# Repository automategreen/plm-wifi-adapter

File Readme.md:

WiFi Adapter for an Insteon PLM
===============
> A Spark Core WiFi adapter for an Insteon PLM
***

With the release of Insteon's newest Hub, Insteon removed the Hub's PLM interface.  This adapter adds secure access over WiFi to an Insteon PLM.

The adapter is a quick demo of what an Insteon compatible open hub could do.  We are currently working on an Open Source Hub with native support for the Insteon RF.

## Insteon Over the Spark Cloud

To improve on the standard Insteon Hub, we've used the awesome [Spark OS](https://www.spark.io/) to extend the PLM interface security to the cloud.  No unencrypted open information here. All messaging pass securely to and from the Spark OS.

### Insteon Message

All Insteon messages are sent as HEX strings.  The HEX strings allow for all Insteon messages to fit within the Spark OS packet restriction.  It also minimizes the logic for the adapter.

Because the HEX is cryptic and requires an in-depth knowledge of the Insteon HEX commands, we're adding support for the adapter to our Node.js module, [home-controller](https://github.com/automategreen/home-controller).

### Sending an Insteon Command

All the Insteon commands can be sent using HEX strings.

For example, to turn an Insteon switch on, you send a direct command to turn on the device.

```
$ spark call 0123456789ABCDEFGHI insteon 0262AABBCC0F117F
8
```

- Direct command: 0262
- Device ID: AABBCC
- Flags: 0F
- Action (turn on): 11
- Level (50%): 7F

The light turns on to 50%, and the call returns the number of bytes sent to the PLM. In this case `8`. 

### Receiving an Insteon Event

Now you can control your device, but you want more.  You want notifications in real time of from you devices.  No problem.  You can use the Spark OS subscribe to receive Insteon messages from your device.

Here's and example of getting notified of motion detected by a motion sensor.

```
$ spark subscribe insteon 0123456789ABCDEFGHI
Subscribing to "insteon" from 0123456789ABCDEFGHI's stream
Listening to: /v1/devices/0123456789ABCDEFGHI/events/insteon
{"name":"insteon","data":"0250aabbcc000001cf1101","ttl":"60","published_at":"2015-01-12T21:16:48.361Z","coreid":"0123456789ABCDEFGHI"}
```

The data field contains the Insteon message.

- Received command: 0250
- Device ID: AABBCC
- Group: 000001
- Flags: cf
- Action (motion detected): 11

### Insteon Request/Response

If you want to query a device for information, you combine the `call` and `subscribe` together. 

First, make sure you're subscribed.

```
spark subscribe insteon 0123456789ABCDEFGHI
Subscribing to "insteon" from 0123456789ABCDEFGHI's stream
Listening to: /v1/devices/0123456789ABCDEFGHI/events/insteon
```

Then, send the request. For example, get the light level.

```
$ spark call 0123456789ABCDEFGHI insteon 0262aabbcc0f1900
2
```

You'll then receive the Insteon response from the subscription.

```
{"name":"insteon","data":"0250aabbccffffff2f01ff","ttl":"60","published_at":"2015-01-12T21:16:48.361Z","coreid":"0123456789ABCDEFGHI"}
```

Light is on at 100%.  

If your want an easier way, you can use [home-controller](https://github.com/automategreen/home-controller).

## Native PLM Interface

The original Hub had an unsecured PLM interface, which allowed for the same communication on the LAN.  We can duplicate the interface on the Spark Core. By default, this interface is disabled (for security).  To enable it, place a simple Spark OS call.

```
spark call 55ff71066678505519401367 config plm=true
```

This call enables the PLM TCP interface (port 9761).

You can now use the adapter with legacy software solution (including our [home-controller](https://github.com/automategreen/home-controller) Node.js package).

## Feedback & Support

Please let us know if you like this concept. We're looking for feedback on creating an open Hub.  Send us an email, [support@automategreen.com](mailto:support@automategreen.com), or a tweet, [@AutomateGreen](https://twitter.com/AutomateGreen).

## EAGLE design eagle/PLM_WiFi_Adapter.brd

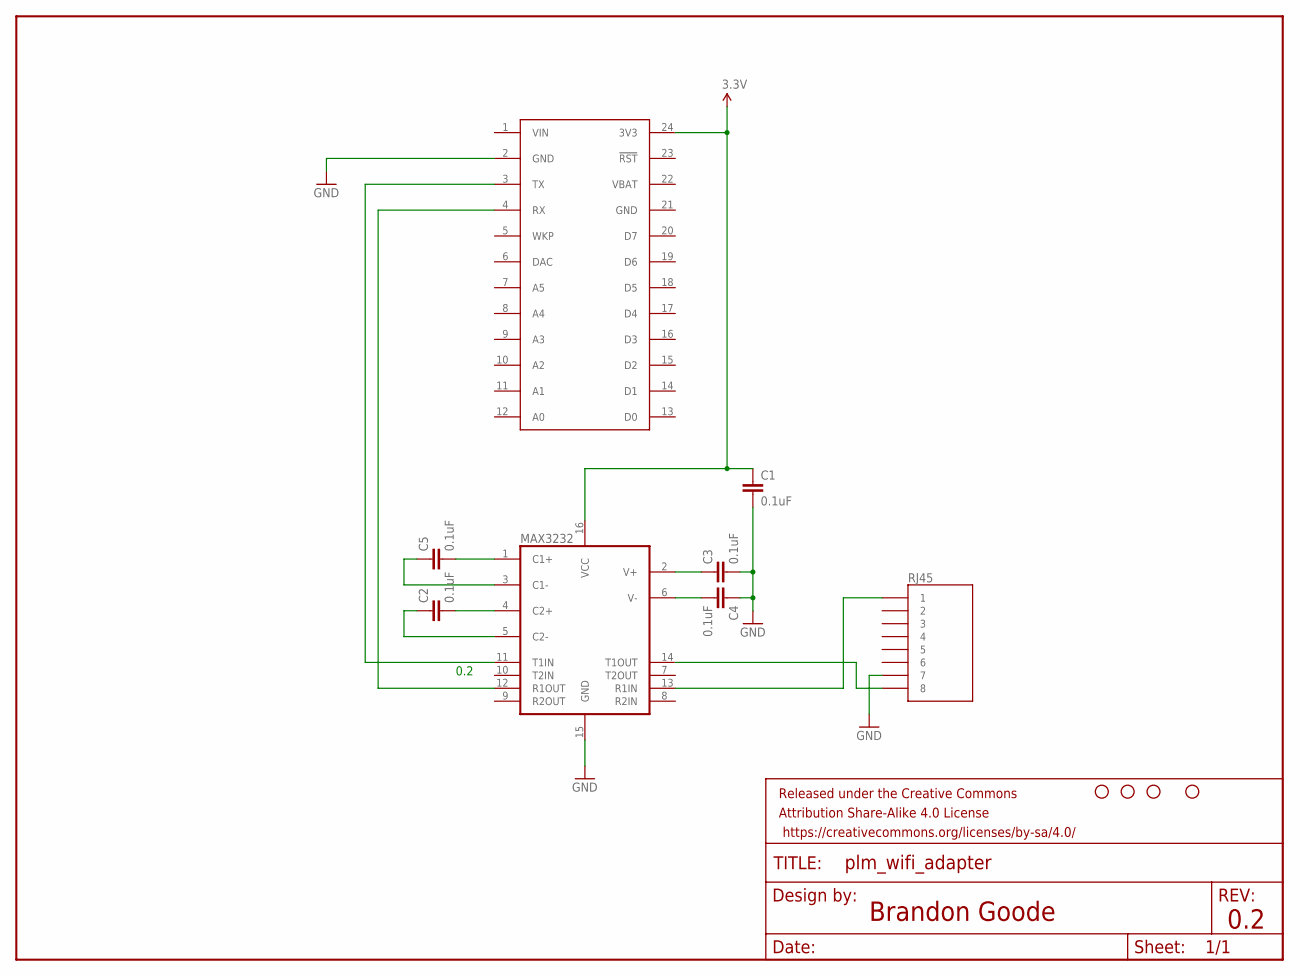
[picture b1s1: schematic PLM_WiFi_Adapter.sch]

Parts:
C1, C2, C3, C4, C5: 0.1uF; 0603-CAP
FRAME1: FRAME-LETTER; CREATIVE_COMMONS
MAX3232: MAX232TSSOP; TSSOP16
RJ45: RJ45-8PTH; RJ45-8
SPARK: SPARK_CORECORE; SPARK_CORE
STANDOFF1, STANDOFF2, STANDOFF3, STANDOFF4: STAND-OFF

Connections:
3.3V: C1.1, MAX3232.16 (VCC), SPARK.24 (3V3)
GND: C1.2, C3.2, C4.1, MAX3232.15 (GND), RJ45.7, SPARK.2 (GND), SPARK.21 (GND)
unnamed: C5.2, MAX3232.1 (C1+)
unnamed: C3.1, MAX3232.2 (V+)
unnamed: C4.2, MAX3232.6 (V-)
unnamed: MAX3232.14 (T1OUT), RJ45.8
unnamed: MAX3232.13 (R1IN), RJ45.1
unnamed: C5.1, MAX3232.3 (C1-)
unnamed: C2.2, MAX3232.4 (C2+)
unnamed: C2.1, MAX3232.5 (C2-)
unnamed: MAX3232.11 (T1IN), SPARK.3 (TX)
unnamed: MAX3232.12 (R1OUT), SPARK.4 (RX)
VBAT: SPARK.22 (VBAT)
VIN: SPARK.1 (VIN)

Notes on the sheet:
0.2
Brandon Goode

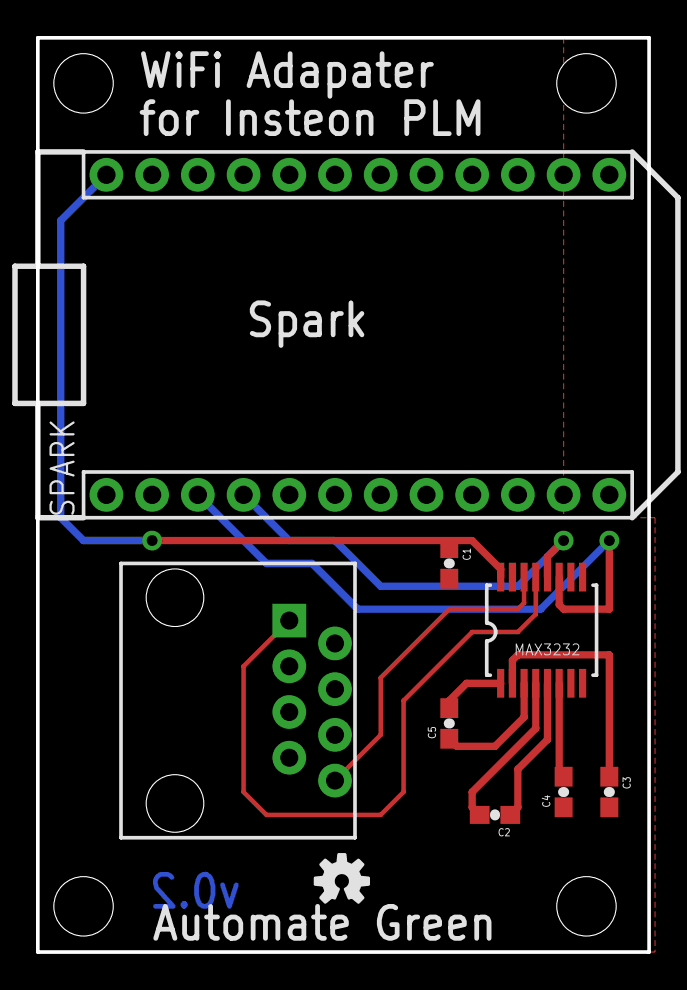
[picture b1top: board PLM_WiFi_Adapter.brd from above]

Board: 2 copper layers, 34.0 x 50.8 mm, 14 parts (0 on the bottom side), 12 nets.

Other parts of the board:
U$1: OSHW-LOGO-S

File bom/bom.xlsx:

Automate Green
WiFi Adapter for Insteon PLM
v0.2
Minimum Specification | Package/Case | Quanty | Part Designator | MFG. | MFG. PN | DigiKey PN
0.1" Female Header (optional) |  | 2 |  |  |  | S7045-ND
RJ45 Connector |  | 1 |  |  |  | 609-1046-ND
0.1uF Ceramic Capacitor - 25V 10% X7R | 0603 | 5 | C1, C2, C3, C4, C5 |  |  | 490-1524-1-ND
3.3v RS232 Transceiver | 16TSSOP | 1 |  | Maxim | MAX3232CUE+ | MAX3232CUE+-ND

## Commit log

2015-01-13 v0.2
2015-01-22 [fix] correct parsing and disabled PLM TCP server

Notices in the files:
parts and their libraries:
SparkFun-Passives: Licensing: Creative Commons ShareAlike 4.0 International - https://creativecommons.org/licenses/by-sa/4.0
SparkFun-Aesthetics: Released under the Creative Commons Attribution Share-Alike 4.0 License
SparkFun-Aesthetics: https://creativecommons.org/licenses/by-sa/4.0
